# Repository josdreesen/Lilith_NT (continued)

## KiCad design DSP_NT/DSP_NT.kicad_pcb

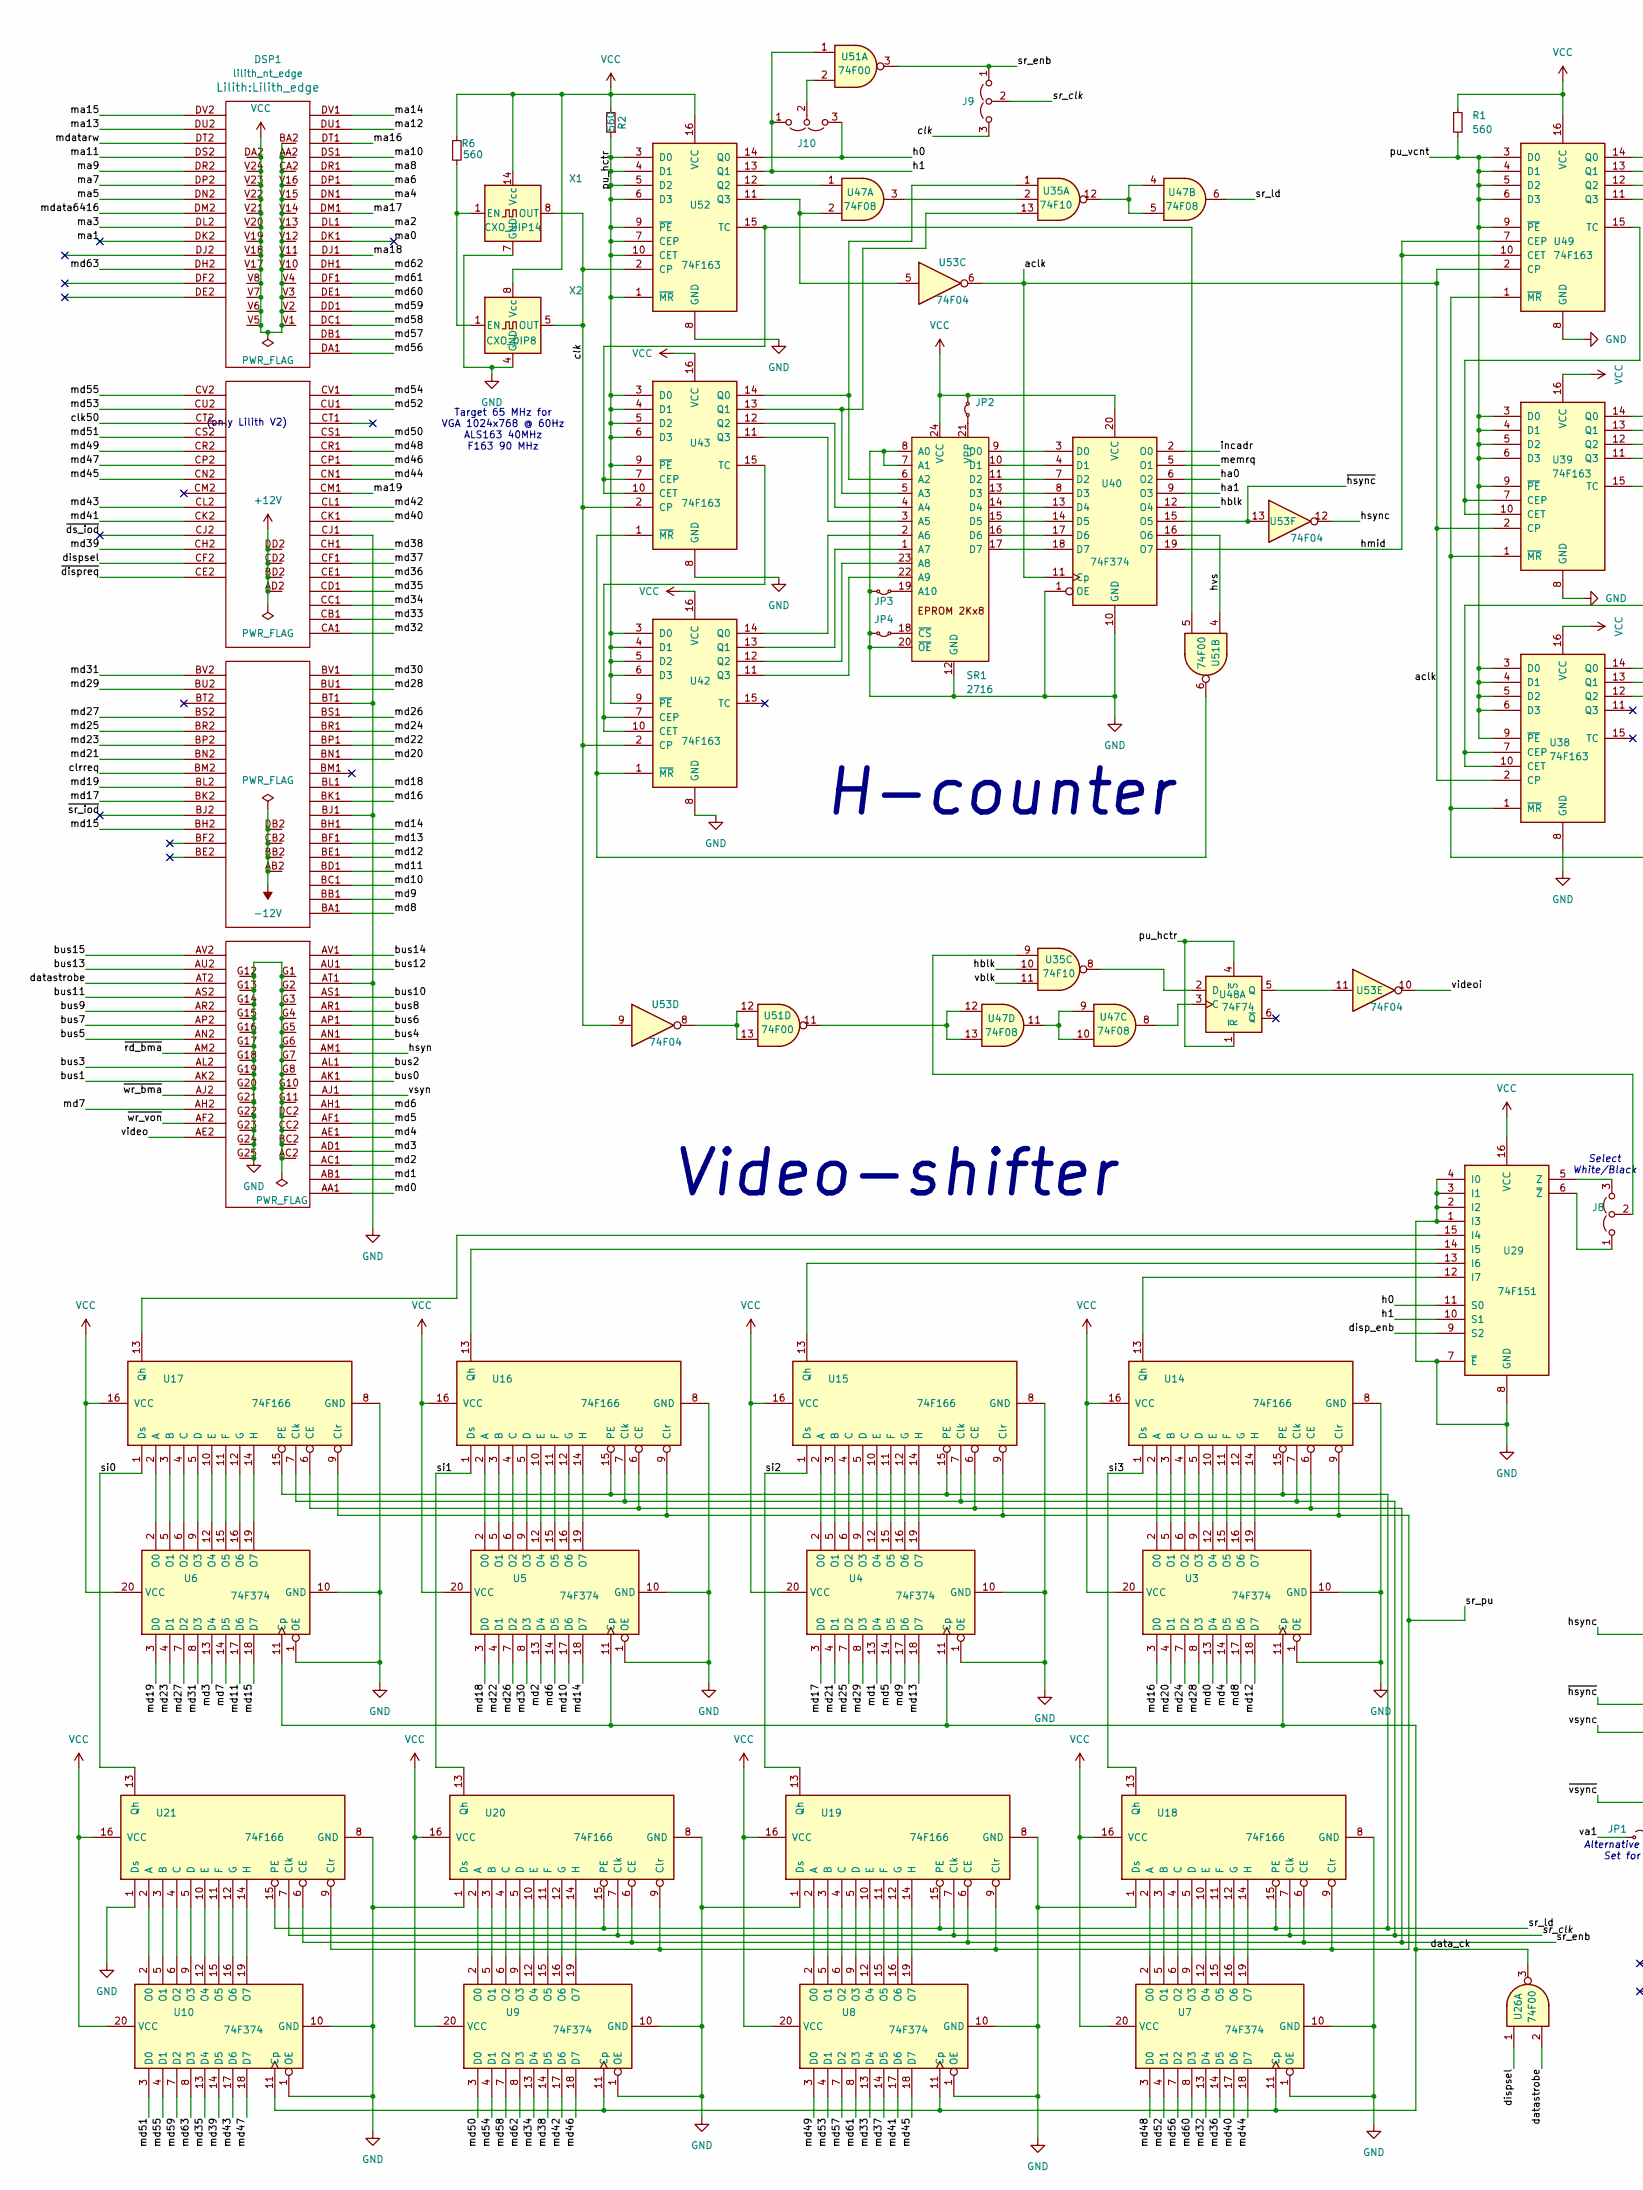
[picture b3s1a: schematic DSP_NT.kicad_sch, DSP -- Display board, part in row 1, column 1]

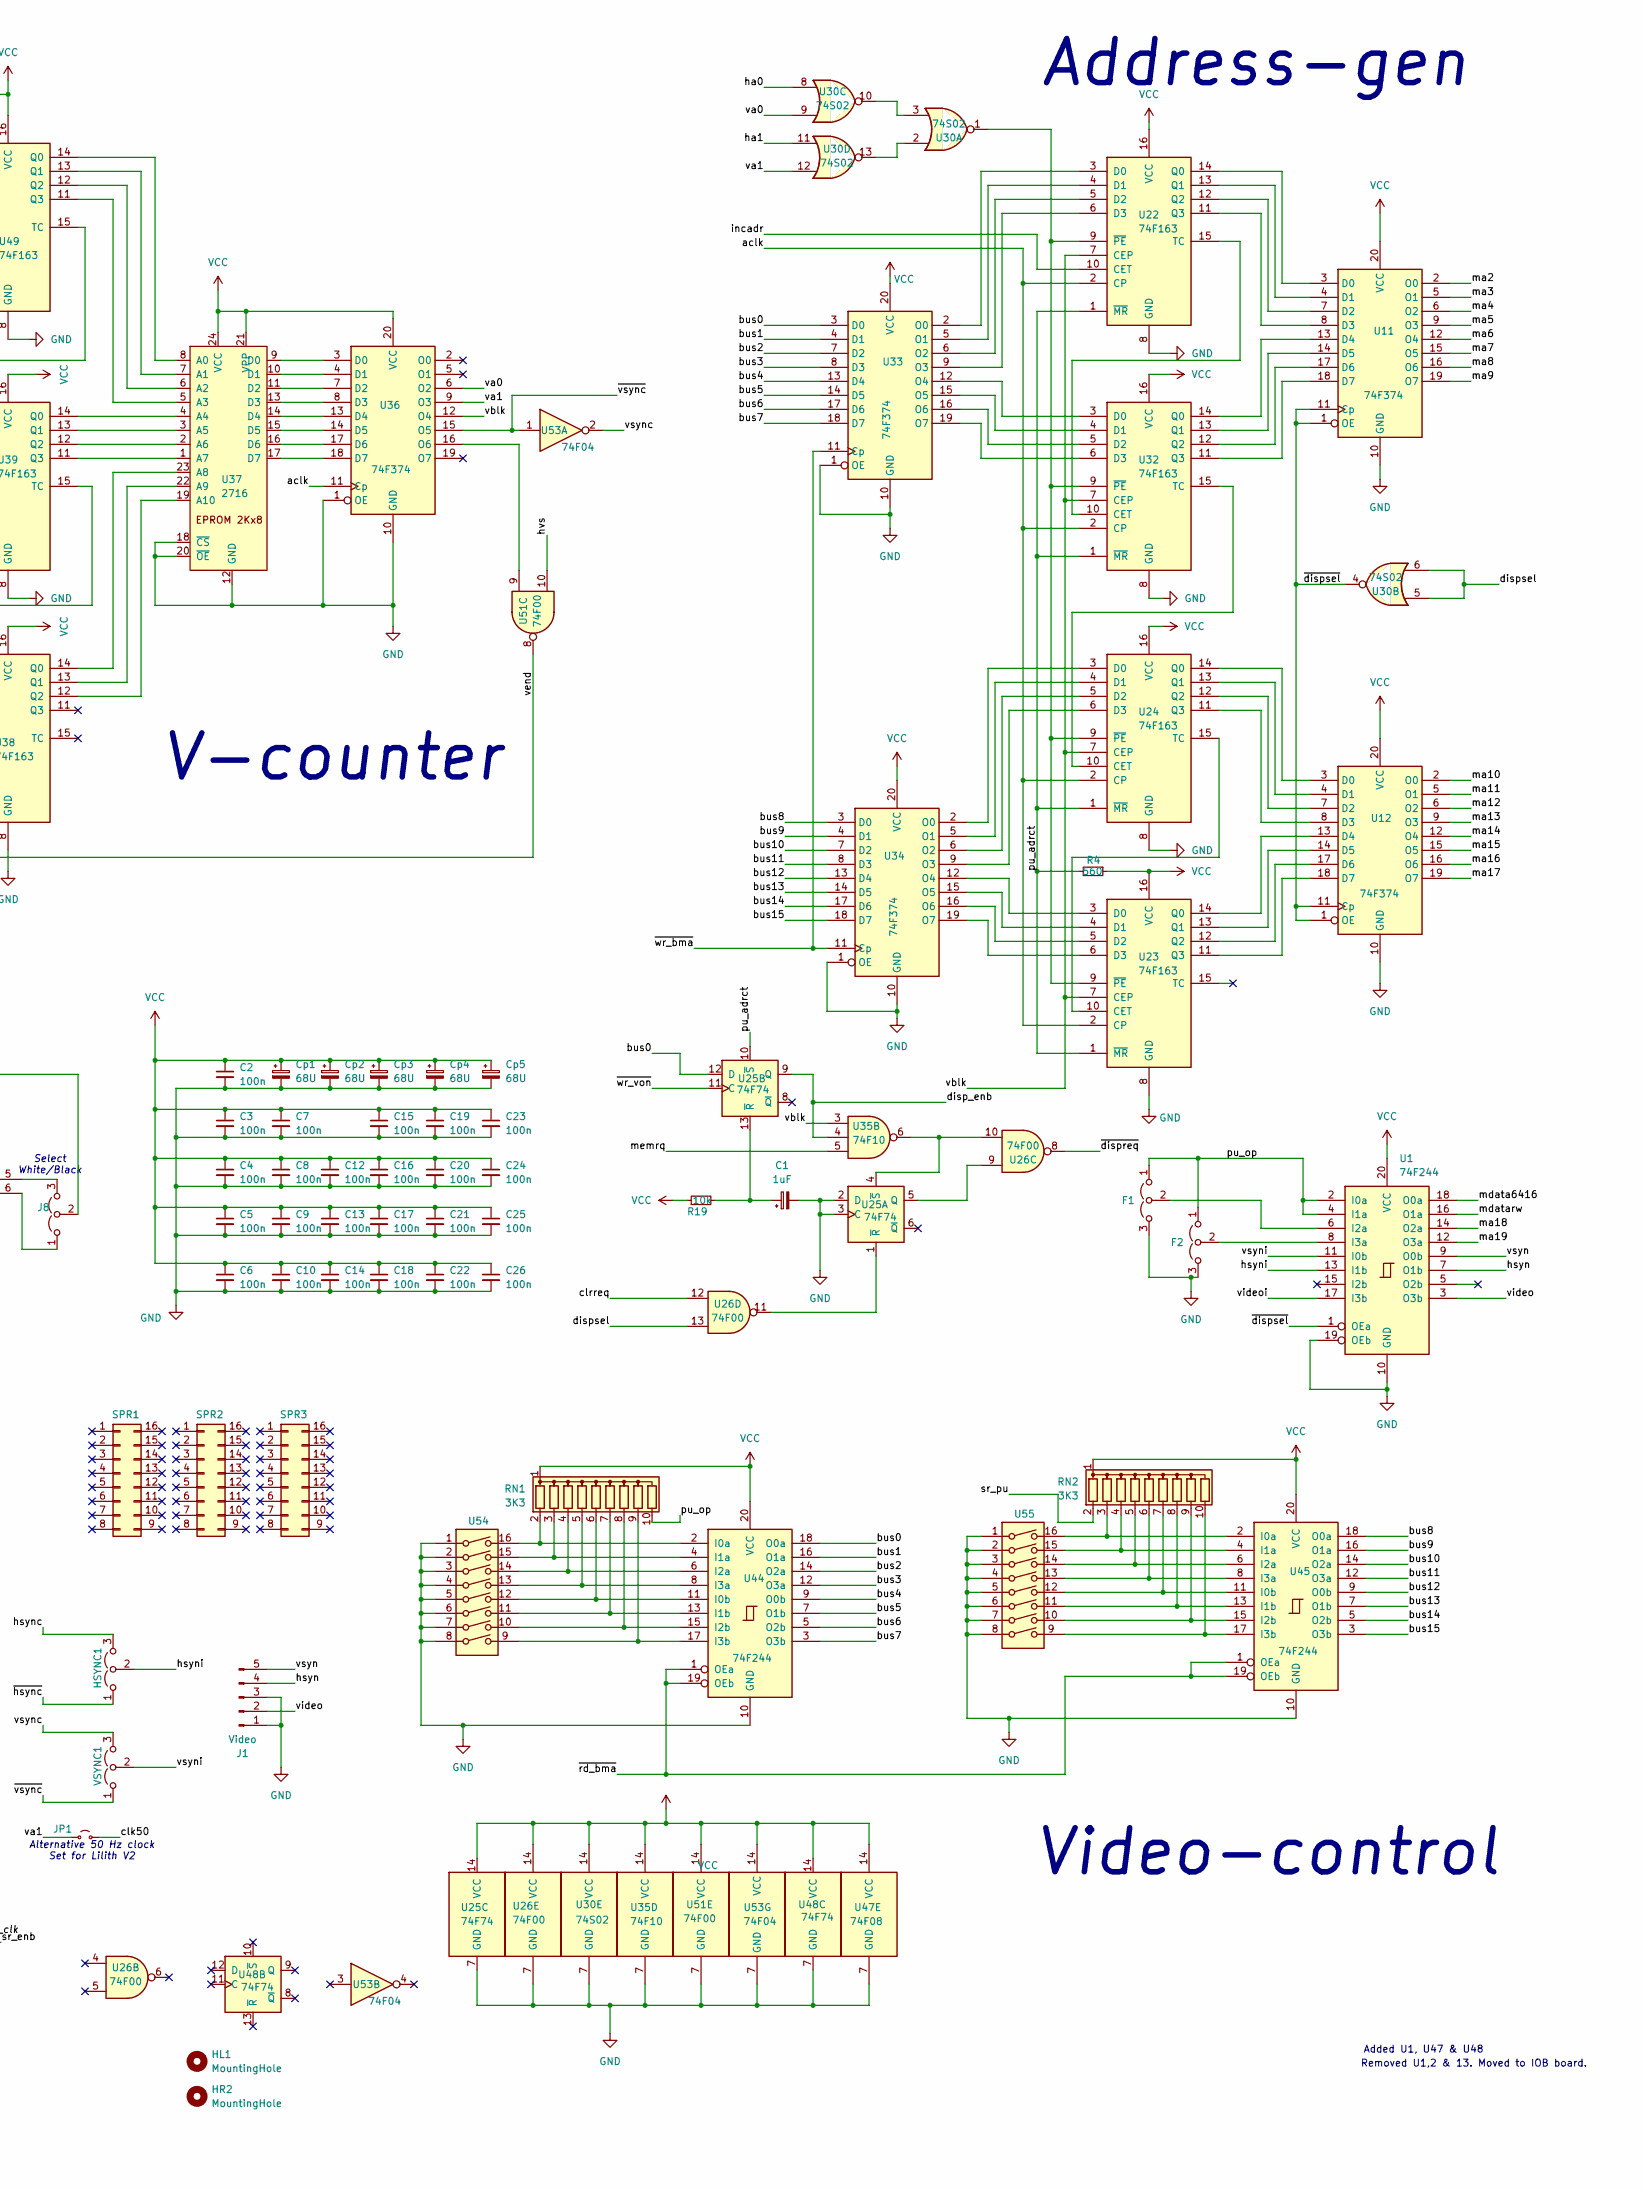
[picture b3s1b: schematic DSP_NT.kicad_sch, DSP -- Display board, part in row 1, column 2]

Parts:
C1: 1uF; CP_Radial_D4.0mm_P2.00mm
C2, C3, C4, C5, C6, C7, C8, C9, C10, C12, C13, C14, C15, C16, C17, C18, C19, C20, C21, C22, C23, C24, C25, C26: 100n; C_1206_3216Metric_Pad1.33x1.80mm_HandSolder
Cp1, Cp2, Cp3, Cp4, Cp5: 68U; CP_PHP
DSP1: lilith_nt_edge; Lilith_edge
F1, F2: Jumper_3_Open; PinHeader_1x03_P2.54mm_Vertical
HL1: MountingHole; Handle
HR2: MountingHole; Handle
HSYNC1: Jumper_3_Open; PinHeader_1x03_P2.54mm_Vertical
J1: Video; PinSocket_1x05_P2.54mm_Vertical
J8: Jumper_3_Open; SW_Push_1P2T_Vertical_E-Switch_800UDP8P1A1M6
J9, J10: Jumper_3_Open; PinHeader_1x03_P2.54mm_Vertical
JP1: Jumper_2_Small_Open; PinHeader_1x02_P2.54mm_Vertical
JP2, JP3, JP4: Jumper_2_Small_Bridged; SolderJumper-2_P1.3mm_Bridged_RoundedPad1.0x1.5mm
R1, R2, R4, R6: 560; R_Axial_DIN0207_L6.3mm_D2.5mm_P10.16mm_Horizontal
R19: 10k; R_Axial_DIN0207_L6.3mm_D2.5mm_P10.16mm_Horizontal
RN1, RN2: 3K3; R_Array_SIP10
SPR1, SPR2, SPR3: Conn_02x08_Counter_Clockwise; DIP-16_W7.62mm
SR1: 2716; DIP-24_W15.24mm_Socket
U1, U44, U45: 74F244; DIP-20_W7.62mm
U3, U4, U5, U6, U7, U8, U9, U10, U11, U12, U33, U34, U36, U40: 74F374; DIP-20_W7.62mm
U14, U15, U16, U17, U18, U19, U20, U21: 74F166; DIP-16_W7.62mm
U22, U23, U24, U32, U38, U39, U42, U43, U49, U52: 74F163; DIP-16_W7.62mm
U25, U48: 74F74; DIP-14_W7.62mm
U26, U51: 74F00; DIP-14_W7.62mm
U29: 74F151; DIP-16_W7.62mm
U30: 74S02; DIP-14_W7.62mm
U35: 74F10; DIP-14_W7.62mm
U37: 2716; DIP-24_W15.24mm_Socket
U47: 74F08; DIP-14_W7.62mm
U53: 74F04; DIP-14_W7.62mm
U54, U55: SW_DIP_x08; DIP-16_W7.62mm
VSYNC1: Jumper_3_Open; PinHeader_1x03_P2.54mm_Vertical
X1: CXO_DIP14; Oscillator_DIP-14
X2: CXO_DIP8; Oscillator_DIP-8

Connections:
+12V: DSP1.AD2, DSP1.BD2, DSP1.CD2, DSP1.DD2
-12V: DSP1.AB2, DSP1.BB2, DSP1.CB2, DSP1.DB2
/aclk: U22.2 (CP), U23.2 (CP), U24.2 (CP), U32.2 (CP), U36.11 (Cp), U38.2 (CP), U39.2 (CP), U40.11 (Cp), U49.2 (CP), U53.6
/bus0: DSP1.AK1, U25.12 (D), U33.3 (D0), U44.18 (O0a)
/bus1: DSP1.AK2, U33.4 (D1), U44.16 (O1a)
/bus2: DSP1.AL1, U33.7 (D2), U44.14 (O2a)
/bus3: DSP1.AL2, U33.8 (D3), U44.12 (O3a)
/bus4: DSP1.AN1, U33.13 (D4), U44.9 (O0b)
/bus5: DSP1.AN2, U33.14 (D5), U44.7 (O1b)
/bus6: DSP1.AP1, U33.17 (D6), U44.5 (O2b)
/bus7: DSP1.AP2, U33.18 (D7), U44.3 (O3b)
/bus8: DSP1.AR1, U34.3 (D0), U45.18 (O0a)
/bus9: DSP1.AR2, U34.4 (D1), U45.16 (O1a)
/bus10: DSP1.AS1, U34.7 (D2), U45.14 (O2a)
/bus11: DSP1.AS2, U34.8 (D3), U45.12 (O3a)
/bus12: DSP1.AU1, U34.13 (D4), U45.9 (O0b)
/bus13: DSP1.AU2, U34.14 (D5), U45.7 (O1b)
/bus14: DSP1.AV1, U34.17 (D6), U45.5 (O2b)
/bus15: DSP1.AV2, U34.18 (D7), U45.3 (O3b)
/clk: J9.3 (B), U42.2 (CP), U43.2 (CP), U52.2 (CP), U53.9, X1.8 (OUT), X2.5 (OUT)
/clk50: DSP1.CT2, JP1.2 (B)
/clrreq: DSP1.BM2, U26.12
/data_ck: U3.11 (Cp), U4.11 (Cp), U5.11 (Cp), U6.11 (Cp), U7.11 (Cp), U8.11 (Cp), U9.11 (Cp), U10.11 (Cp), U26.3
/datastrobe: DSP1.AT2, U26.2
/disp_enb: U25.9 (Q), U29.9 (S2), U35.4
/dispsel: DSP1.CF2, U26.1, U26.13, U30.5, U30.6
/h0: J10.3 (B), U29.11 (S0), U52.14 (Q0)
/h1: J10.1 (A), U29.10 (S1), U51.1, U52.13 (Q1)
/ha0: U30.8, U40.6 (O2)
/ha1: U30.11, U40.9 (O3)
/hblk: U35.10, U40.12 (O4)
/hmid: U40.19 (O7), U49.7 (CEP), U49.10 (CET)
/hsyn: DSP1.AM1, J1.4, U1.7 (O1b)
/hsync: HSYNC1.3 (B), U53.12
/hsyni: HSYNC1.2 (C), U1.13 (I1b)
/hvs: U40.16 (O6), U51.4, U51.10
/incadr: U22.10 (CET), U40.2 (O0)
/ma0: DSP1.DK1
/ma1: DSP1.DK2
/ma2: DSP1.DL1, U11.2 (O0)
/ma3: DSP1.DL2, U11.5 (O1)
/ma4: DSP1.DN1, U11.6 (O2)
/ma5: DSP1.DN2, U11.9 (O3)
/ma6: DSP1.DP1, U11.12 (O4)
/ma7: DSP1.DP2, U11.15 (O5)
/ma8: DSP1.DR1, U11.16 (O6)
/ma9: DSP1.DR2, U11.19 (O7)
/ma10: DSP1.DS1, U12.2 (O0)
/ma11: DSP1.DS2, U12.5 (O1)
/ma12: DSP1.DU1, U12.6 (O2)
/ma13: DSP1.DU2, U12.9 (O3)
/ma14: DSP1.DV1, U12.12 (O4)
/ma15: DSP1.DV2, U12.15 (O5)
/ma16: DSP1.DT1, U12.16 (O6)
/ma17: DSP1.DM1, U12.19 (O7)
/ma18: DSP1.DJ1, U1.14 (O2a)
/ma19: DSP1.CM1, U1.12 (O3a)
/md0: DSP1.AA1, U3.13 (D4)
/md1: DSP1.AB1, U4.13 (D4)
/md2: DSP1.AC1, U5.13 (D4)
/md3: DSP1.AD1, U6.13 (D4)
/md4: DSP1.AE1, U3.14 (D5)
/md5: DSP1.AF1, U4.14 (D5)
/md6: DSP1.AH1, U5.14 (D5)
/md7: DSP1.AH2, U6.14 (D5)
/md8: DSP1.BA1, U3.17 (D6)
/md9: DSP1.BB1, U4.17 (D6)
/md10: DSP1.BC1, U5.17 (D6)
/md11: DSP1.BD1, U6.17 (D6)
/md12: DSP1.BE1, U3.18 (D7)
/md13: DSP1.BF1, U4.18 (D7)
/md14: DSP1.BH1, U5.18 (D7)
/md15: DSP1.BH2, U6.18 (D7)
/md16: DSP1.BK1, U3.3 (D0)
/md17: DSP1.BK2, U4.3 (D0)
/md18: DSP1.BL1, U5.3 (D0)
/md19: DSP1.BL2, U6.3 (D0)
/md20: DSP1.BN1, U3.4 (D1)
/md21: DSP1.BN2, U4.4 (D1)
/md22: DSP1.BP1, U5.4 (D1)
/md23: DSP1.BP2, U6.4 (D1)
/md24: DSP1.BR1, U3.7 (D2)
/md25: DSP1.BR2, U4.7 (D2)
/md26: DSP1.BS1, U5.7 (D2)
/md27: DSP1.BS2, U6.7 (D2)
/md28: DSP1.BU1, U3.8 (D3)
/md29: DSP1.BU2, U4.8 (D3)
/md30: DSP1.BV1, U5.8 (D3)
/md31: DSP1.BV2, U6.8 (D3)
/md32: DSP1.CA1, U7.13 (D4)
/md33: DSP1.CB1, U8.13 (D4)
/md34: DSP1.CC1, U9.13 (D4)
/md35: DSP1.CD1, U10.13 (D4)
/md36: DSP1.CE1, U7.14 (D5)
/md37: DSP1.CF1, U8.14 (D5)
/md38: DSP1.CH1, U9.14 (D5)
/md39: DSP1.CH2, U10.14 (D5)
/md40: DSP1.CK1, U7.17 (D6)
/md41: DSP1.CK2, U8.17 (D6)
/md42: DSP1.CL1, U9.17 (D6)
/md43: DSP1.CL2, U10.17 (D6)
/md44: DSP1.CN1, U7.18 (D7)
/md45: DSP1.CN2, U8.18 (D7)
/md46: DSP1.CP1, U9.18 (D7)
/md47: DSP1.CP2, U10.18 (D7)
/md48: DSP1.CR1, U7.3 (D0)
/md49: DSP1.CR2, U8.3 (D0)
/md50: DSP1.CS1, U9.3 (D0)
/md51: DSP1.CS2, U10.3 (D0)
/md52: DSP1.CU1, U7.4 (D1)
/md53: DSP1.CU2, U8.4 (D1)
/md54: DSP1.CV1, U9.4 (D1)
/md55: DSP1.CV2, U10.4 (D1)
/md56: DSP1.DA1, U7.7 (D2)
/md57: DSP1.DB1, U8.7 (D2)
/md58: DSP1.DC1, U9.7 (D2)
/md59: DSP1.DD1, U10.7 (D2)
/md60: DSP1.DE1, U7.8 (D3)
/md61: DSP1.DF1, U8.8 (D3)
/md62: DSP1.DH1, U9.8 (D3)
/md63: DSP1.DH2, U10.8 (D3)
/mdata6416: DSP1.DM2, U1.18 (O0a)
/mdatarw: DSP1.DT2, U1.16 (O1a)
/memrq: U35.5, U40.5 (O1)
/pu_adrct: R4.2, U22.1 (~MR), U23.1 (~MR), U24.1 (~MR), U25.10 (~S), U32.1 (~MR)
/pu_hctr: R2.1, U42.3 (D0), U42.4 (D1), U42.5 (D2), U42.6 (D3), U42.9 (~PE), U43.3 (D0), U43.4 (D1), U43.5 (D2), U43.6 (D3), U43.9 (~PE), U48.1 (~R), U48.4 (~S), U52.1 (~MR), U52.3 (D0), U52.4 (D1), U52.5 (D2), U52.6 (D3), U52.7 (CEP), U52.9 (~PE), U52.10 (CET)
/pu_op: F1.1 (A), F2.1 (A), RN1.10 (R9), U1.2 (I0a), U1.4 (I1a); also elsewhere on the board
/pu_vcnt: R1.2, U38.3 (D0), U38.4 (D1), U38.5 (D2), U38.6 (D3), U38.9 (~PE), U39.3 (D0), U39.4 (D1), U39.5 (D2), U39.6 (D3), U39.9 (~PE), U49.3 (D0), U49.4 (D1), U49.5 (D2), U49.6 (D3), U49.9 (~PE)
/si0: U17.1 (Ds), U21.13 (Qh)
/si1: U16.1 (Ds), U20.13 (Qh)
/si2: U15.1 (Ds), U19.13 (Qh)
/si3: U14.1 (Ds), U18.13 (Qh)
/sr_clk: J9.2 (C), U14.7 (Clk), U15.7 (Clk), U16.7 (Clk), U17.7 (Clk), U18.7 (Clk), U19.7 (Clk), U20.7 (Clk), U21.7 (Clk)
/sr_enb: J9.1 (A), U14.6 (CE), U15.6 (CE), U16.6 (CE), U17.6 (CE), U18.6 (CE), U19.6 (CE), U20.6 (CE), U21.6 (CE), U51.3
/sr_ld: U14.15 (PE), U15.15 (PE), U16.15 (PE), U17.15 (PE), U18.15 (PE), U19.15 (PE), U20.15 (PE), U21.15 (PE), U47.6
/sr_pu: RN2.2 (R1), U14.9 (Clr), U15.9 (Clr), U16.9 (Clr), U17.9 (Clr), U18.9 (Clr), U19.9 (Clr), U20.9 (Clr), U21.9 (Clr)
/va0: U30.9, U36.6 (O2)
/va1: JP1.1 (A), U30.12, U36.9 (O3)
/vblk: U22.7 (CEP), U23.7 (CEP), U24.7 (CEP), U32.7 (CEP), U35.3, U35.11, U36.12 (O4)
/vend: U38.1 (~MR), U39.1 (~MR), U49.1 (~MR), U51.8
/video: DSP1.AE2, J1.2, U1.3 (O3b)
/videoi: U1.17 (I3b), U53.10
/vsyn: DSP1.AJ1, J1.5, U1.9 (O0b)
/vsync: U53.2, VSYNC1.3 (B)
/vsyni: U1.11 (I0b), VSYNC1.2 (C)
/~dispreq: DSP1.CE2, U26.8
/~dispsel: U1.1 (OEa), U11.1 (OE), U11.11 (Cp), U12.1 (OE), U12.11 (Cp), U30.4
/~ds_iod: DSP1.CJ2
/~hsync: HSYNC1.1 (A), U40.15 (O5), U53.13
/~rd_bma: DSP1.AM2, U44.1 (OEa), U44.19 (OEb), U45.1 (OEa), U45.19 (OEb)
/~sr_iod: DSP1.BJ2
/~vsync: U36.15 (O5), U53.1, VSYNC1.1 (A)
/~wr_bma: DSP1.AJ2, U33.11 (Cp), U34.11 (Cp)
/~wr_von: DSP1.AF2, U25.11 (C)
GND: C1.2, C2.2, C3.2, C4.2, C5.2, C6.2, C7.2, C8.2, C9.2, C10.2, C12.2, C13.2, C14.2, C15.2, C16.2, C17.2, C18.2, C19.2, C20.2, C21.2, C22.2, C23.2, C24.2, C25.2, C26.2, Cp1.2, Cp2.2, Cp3.2, Cp4.2, Cp5.2, DSP1.AC2, DSP1.AT1, DSP1.BC2, DSP1.BJ1, DSP1.BT1, DSP1.CC2, DSP1.CJ1, DSP1.DC2, DSP1.G1 (GND), DSP1.G2 (GND), DSP1.G3 (GND), DSP1.G4 (GND), DSP1.G5 (GND), DSP1.G6 (GND), DSP1.G7 (GND), DSP1.G8 (GND), DSP1.G10, DSP1.G11, DSP1.G12, DSP1.G13, DSP1.G14, DSP1.G15, DSP1.G16, DSP1.G17, DSP1.G18, DSP1.G19, DSP1.G20, DSP1.G21, DSP1.G22, DSP1.G23, DSP1.G24, DSP1.G25, F1.3 (B), F2.3 (B), J1.1, J1.3, JP3.2 (B), JP4.2 (B), SR1.7 (A1), SR1.8 (A0), SR1.12 (GND), SR1.20 (~OE), U1.10 (GND), U1.19 (OEb), U3.1 (OE), U3.10 (GND), U4.1 (OE), U4.10 (GND), U5.1 (OE), U5.10 (GND), U6.1 (OE), U6.10 (GND), U7.1 (OE), U7.10 (GND), U8.1 (OE), U8.10 (GND), U9.1 (OE), U9.10 (GND), U10.1 (OE), U10.10 (GND), U11.10 (GND), U12.10 (GND), U14.8 (GND), U15.8 (GND), U16.8 (GND), U17.8 (GND), U18.1 (Ds), U18.8 (GND), U19.1 (Ds), U19.8 (GND), U20.1 (Ds), U20.8 (GND), U21.1 (Ds), U21.8 (GND), U22.8 (GND), U23.8 (GND), U24.8 (GND), U25.2 (D), U25.3 (C), U25.7 (GND), U26.7 (GND), U29.1 (I3), U29.2 (I2), U29.3 (I1), U29.4 (I0), U29.7 (~E), U29.8 (GND), U30.7 (GND), U32.8 (GND), U33.1 (OE), U33.10 (GND), U34.1 (OE), U34.10 (GND), U35.7 (GND), U36.1 (OE), U36.10 (GND), U37.12 (GND), U37.18 (~CS), U37.20 (~OE), U38.8 (GND), U39.8 (GND), U40.1 (OE), U40.10 (GND), U42.8 (GND), U43.8 (GND), U44.10 (GND), U45.10 (GND), U47.7 (GND), U48.7 (GND), U49.8 (GND), U51.7 (GND), U52.8 (GND), U53.7 (GND), U54.1, U54.2, U54.3, U54.4, U54.5, U54.6, U54.7, U54.8, U55.1, U55.2, U55.3, U55.4, U55.5, U55.6, U55.7, U55.8, X1.7 (GND), X2.4 (GND); also elsewhere on the board
unnamed 155: F1.2 (C), U1.6 (I2a); also elsewhere on the board
unnamed 156: F2.2 (C), U1.8 (I3a); also elsewhere on the board
unnamed: J8.1 (A), U29.6 (~Z)
unnamed: J8.3 (B), U29.5 (Z)
unnamed: J8.2 (C), U35.9
unnamed: J10.2 (C), U51.2
unnamed: JP2.1 (A), SR1.21 (VPP)
unnamed: JP3.1 (A), SR1.19 (A10)
unnamed: JP4.1 (A), SR1.18 (~CS)
unnamed: RN1.2 (R1), U44.2 (I0a), U54.16
unnamed: RN1.3 (R2), U44.4 (I1a), U54.15
unnamed: RN1.4 (R3), U44.6 (I2a), U54.14
unnamed: RN1.5 (R4), U44.8 (I3a), U54.13
unnamed: RN1.6 (R5), U44.11 (I0b), U54.12
unnamed: RN1.7 (R6), U44.13 (I1b), U54.11
unnamed: RN1.8 (R7), U44.15 (I2b), U54.10
unnamed: RN1.9 (R8), U44.17 (I3b), U54.9
unnamed: RN2.3 (R2), U45.2 (I0a), U55.16
unnamed: RN2.4 (R3), U45.4 (I1a), U55.15
unnamed: RN2.5 (R4), U45.6 (I2a), U55.14
unnamed: RN2.6 (R5), U45.8 (I3a), U55.13
unnamed: RN2.7 (R6), U45.11 (I0b), U55.12
unnamed: RN2.8 (R7), U45.13 (I1b), U55.11
unnamed: RN2.9 (R8), U45.15 (I2b), U55.10
unnamed: RN2.10 (R9), U45.17 (I3b), U55.9
unnamed: SR1.6 (A2), U35.1, U43.14 (Q0)
unnamed: SR1.5 (A3), U35.13, U43.13 (Q1)
unnamed: SR1.4 (A4), U43.12 (Q2)
unnamed: SR1.3 (A5), U43.11 (Q3)
unnamed: SR1.2 (A6), U42.14 (Q0)
unnamed: SR1.1 (A7), U42.13 (Q1)
unnamed: SR1.23 (A8), U42.12 (Q2)
unnamed: SR1.22 (A9), U42.11 (Q3)
unnamed: SR1.9 (D0), U40.3 (D0)
unnamed: SR1.10 (D1), U40.4 (D1)
unnamed: SR1.11 (D2), U40.7 (D2)
unnamed: SR1.13 (D3), U40.8 (D3)
unnamed: SR1.14 (D4), U40.13 (D4)
unnamed: SR1.15 (D5), U40.14 (D5)
unnamed: SR1.16 (D6), U40.17 (D6)
unnamed: SR1.17 (D7), U40.18 (D7)
unnamed: U10.2 (O0), U21.2 (A)
unnamed: U10.5 (O1), U21.3 (B)
unnamed: U10.6 (O2), U21.4 (C)
unnamed: U10.9 (O3), U21.5 (D)
unnamed: U10.12 (O4), U21.10 (E)
unnamed: U10.15 (O5), U21.11 (F)
unnamed: U10.16 (O6), U21.12 (G)
unnamed: U10.19 (O7), U21.14 (H)
unnamed: U11.3 (D0), U22.14 (Q0)
unnamed: U11.4 (D1), U22.13 (Q1)
unnamed: U11.7 (D2), U22.12 (Q2)
unnamed: U11.8 (D3), U22.11 (Q3)
unnamed: U11.13 (D4), U32.14 (Q0)
unnamed: U11.14 (D5), U32.13 (Q1)
unnamed: U11.17 (D6), U32.12 (Q2)
unnamed: U11.18 (D7), U32.11 (Q3)
unnamed: U12.3 (D0), U24.14 (Q0)
unnamed: U12.4 (D1), U24.13 (Q1)
unnamed: U12.7 (D2), U24.12 (Q2)
unnamed: U12.8 (D3), U24.11 (Q3)
unnamed: U12.13 (D4), U23.14 (Q0)
unnamed: U12.14 (D5), U23.13 (Q1)
unnamed: U12.17 (D6), U23.12 (Q2)
unnamed: U12.18 (D7), U23.11 (Q3)
unnamed: U3.2 (O0), U14.2 (A)
unnamed: U3.5 (O1), U14.3 (B)
unnamed: U3.6 (O2), U14.4 (C)
unnamed: U3.9 (O3), U14.5 (D)
unnamed: U3.12 (O4), U14.10 (E)
unnamed: U3.15 (O5), U14.11 (F)
unnamed: U3.16 (O6), U14.12 (G)
unnamed: U3.19 (O7), U14.14 (H)
unnamed: U14.13 (Qh), U29.12 (I7)
unnamed: U4.2 (O0), U15.2 (A)
unnamed: U4.5 (O1), U15.3 (B)
unnamed: U4.6 (O2), U15.4 (C)
unnamed: U4.9 (O3), U15.5 (D)
unnamed: U4.12 (O4), U15.10 (E)
unnamed: U4.15 (O5), U15.11 (F)
unnamed: U4.16 (O6), U15.12 (G)
unnamed: U4.19 (O7), U15.14 (H)
unnamed: U15.13 (Qh), U29.13 (I6)
unnamed: U5.2 (O0), U16.2 (A)
unnamed: U5.5 (O1), U16.3 (B)
unnamed: U5.6 (O2), U16.4 (C)
unnamed: U5.9 (O3), U16.5 (D)
unnamed: U5.12 (O4), U16.10 (E)
unnamed: U5.15 (O5), U16.11 (F)
unnamed: U5.16 (O6), U16.12 (G)
unnamed: U5.19 (O7), U16.14 (H)
unnamed: U16.13 (Qh), U29.14 (I5)
unnamed: U6.2 (O0), U17.2 (A)
unnamed: U6.5 (O1), U17.3 (B)
unnamed: U6.6 (O2), U17.4 (C)
unnamed: U6.9 (O3), U17.5 (D)
unnamed: U6.12 (O4), U17.10 (E)
unnamed: U6.15 (O5), U17.11 (F)
unnamed: U6.16 (O6), U17.12 (G)
unnamed: U6.19 (O7), U17.14 (H)
unnamed: U17.13 (Qh), U29.15 (I4)
unnamed: U7.2 (O0), U18.2 (A)
unnamed: U7.5 (O1), U18.3 (B)
unnamed: U7.6 (O2), U18.4 (C)
unnamed: U7.9 (O3), U18.5 (D)
unnamed: U7.12 (O4), U18.10 (E)
unnamed: U7.15 (O5), U18.11 (F)
unnamed: U7.16 (O6), U18.12 (G)
unnamed: U7.19 (O7), U18.14 (H)
unnamed: U8.2 (O0), U19.2 (A)
unnamed: U8.5 (O1), U19.3 (B)
unnamed: U8.6 (O2), U19.4 (C)
unnamed: U8.9 (O3), U19.5 (D)
unnamed: U8.12 (O4), U19.10 (E)
unnamed: U8.15 (O5), U19.11 (F)
unnamed: U8.16 (O6), U19.12 (G)
unnamed: U8.19 (O7), U19.14 (H)
unnamed: U9.2 (O0), U20.2 (A)
unnamed: U9.5 (O1), U20.3 (B)
unnamed: U9.6 (O2), U20.4 (C)
unnamed: U9.9 (O3), U20.5 (D)
unnamed: U9.12 (O4), U20.10 (E)
unnamed: U9.15 (O5), U20.11 (F)
unnamed: U9.16 (O6), U20.12 (G)
unnamed: U9.19 (O7), U20.14 (H)
unnamed: U22.3 (D0), U33.2 (O0)
unnamed: U22.4 (D1), U33.5 (O1)
unnamed: U22.5 (D2), U33.6 (O2)
unnamed: U22.6 (D3), U33.9 (O3)
unnamed: U22.15 (TC), U32.10 (CET)
unnamed: U22.9 (~PE), U23.9 (~PE), U24.9 (~PE), U30.1, U32.9 (~PE)
unnamed: U23.10 (CET), U24.15 (TC)
unnamed: U23.3 (D0), U34.12 (O4)
unnamed: U23.4 (D1), U34.15 (O5)
unnamed: U23.5 (D2), U34.16 (O6)
unnamed: U23.6 (D3), U34.19 (O7)
unnamed: U24.10 (CET), U32.15 (TC)
unnamed: U24.3 (D0), U34.2 (O0)
unnamed: U24.4 (D1), U34.5 (O1)
unnamed: U24.5 (D2), U34.6 (O2)
unnamed: U24.6 (D3), U34.9 (O3)
unnamed: U25.5 (Q), U26.9
unnamed: U25.1 (~R), U26.11
unnamed: U25.4 (~S), U26.10, U35.6
unnamed: C1.1, R19.2, U25.13 (~R)
unnamed: U30.3, U30.10
unnamed: U30.2, U30.13
unnamed: U32.3 (D0), U33.12 (O4)
unnamed: U32.4 (D1), U33.15 (O5)
unnamed: U32.5 (D2), U33.16 (O6)
unnamed: U32.6 (D3), U33.19 (O7)
unnamed: U35.2, U47.3
unnamed: U35.12, U47.4, U47.5
unnamed: U36.3 (D0), U37.9 (D0)
unnamed: U36.4 (D1), U37.10 (D1)
unnamed: U36.7 (D2), U37.11 (D2)
unnamed: U36.8 (D3), U37.13 (D3)
unnamed: U36.13 (D4), U37.14 (D4)
unnamed: U36.14 (D5), U37.15 (D5)
unnamed: U36.17 (D6), U37.16 (D6)
unnamed: U36.18 (D7), U37.17 (D7)
unnamed: U36.16 (O6), U51.9
unnamed: U37.8 (A0), U49.14 (Q0)
unnamed: U37.7 (A1), U49.13 (Q1)
unnamed: U37.6 (A2), U49.12 (Q2)
unnamed: U37.5 (A3), U49.11 (Q3)
unnamed: U37.4 (A4), U39.14 (Q0)
unnamed: U37.3 (A5), U39.13 (Q1)
unnamed: U37.2 (A6), U39.12 (Q2)
unnamed: U37.1 (A7), U39.11 (Q3)
unnamed: U37.23 (A8), U38.14 (Q0)
unnamed: U37.22 (A9), U38.13 (Q1)
unnamed: U37.19 (A10), U38.12 (Q2)
unnamed: U38.7 (CEP), U38.10 (CET), U39.15 (TC)
unnamed: U39.7 (CEP), U39.10 (CET), U49.15 (TC)
unnamed: U42.7 (CEP), U42.10 (CET), U43.15 (TC)
unnamed: U42.1 (~MR), U43.1 (~MR), U51.6
unnamed: U43.7 (CEP), U43.10 (CET), U51.5, U52.15 (TC)
unnamed: U47.9, U47.10, U47.11
unnamed: U47.12, U47.13, U51.11
unnamed: U47.8, U48.3 (C)
unnamed: U35.8, U48.2 (D)
unnamed: U48.5 (Q), U53.11
unnamed: U51.12, U51.13, U53.8
unnamed: U47.1, U52.12 (Q2)
unnamed: U47.2, U52.11 (Q3), U53.5
unnamed: R6.2, X1.1 (EN), X2.1 (EN)
VCC: C2.1, C3.1, C4.1, C5.1, C6.1, C7.1, C8.1, C9.1, C10.1, C12.1, C13.1, C14.1, C15.1, C16.1, C17.1, C18.1, C19.1, C20.1, C21.1, C22.1, C23.1, C24.1, C25.1, C26.1, Cp1.1, Cp2.1, Cp3.1, Cp4.1, Cp5.1, DSP1.AA2, DSP1.BA2, DSP1.CA2, DSP1.DA2, DSP1.V1 (VCC), DSP1.V2 (VCC), DSP1.V3 (VCC), DSP1.V4 (VCC), DSP1.V5 (VCC), DSP1.V6 (VCC), DSP1.V7 (VCC), DSP1.V8 (VCC), DSP1.V10, DSP1.V11, DSP1.V12, DSP1.V13, DSP1.V14, DSP1.V15, DSP1.V16, DSP1.V17, DSP1.V18, DSP1.V19, DSP1.V20, DSP1.V21, DSP1.V22, DSP1.V23, DSP1.V24, JP2.2 (B), R1.1, R2.2, R4.1, R6.1, R19.1, RN1.1 (common), RN2.1 (common), SR1.24 (VCC), U1.20 (VCC), U3.20 (VCC), U4.20 (VCC), U5.20 (VCC), U6.20 (VCC), U7.20 (VCC), U8.20 (VCC), U9.20 (VCC), U10.20 (VCC), U11.20 (VCC), U12.20 (VCC), U14.16 (VCC), U15.16 (VCC), U16.16 (VCC), U17.16 (VCC), U18.16 (VCC), U19.16 (VCC), U20.16 (VCC), U21.16 (VCC), U22.16 (VCC), U23.16 (VCC), U24.16 (VCC), U25.14 (VCC), U26.14 (VCC), U29.16 (VCC), U30.14 (VCC), U32.16 (VCC), U33.20 (VCC), U34.20 (VCC), U35.14 (VCC), U36.20 (VCC), U37.21 (VPP), U37.24 (VCC), U38.16 (VCC), U39.16 (VCC), U40.20 (VCC), U42.16 (VCC), U43.16 (VCC), U44.20 (VCC), U45.20 (VCC), U47.14 (VCC), U48.14 (VCC), U49.16 (VCC), U51.14 (VCC), U52.16 (VCC), U53.14 (VCC), X1.14 (Vcc), X2.8 (Vcc)

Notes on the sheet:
Address-gen
Target 65 MHz for VGA 1024x768 @ 60Hz ALS163 40MHz F163 90 MHz
Added U1, U47 & U48
Alternative 50 Hz clock Set for Lilith V2
Removed U1,2 & 13. Moved to IOB board.
Video-shifter
(only Lilith V2)
H-counter
Video-control
Select White/Black
V-counter

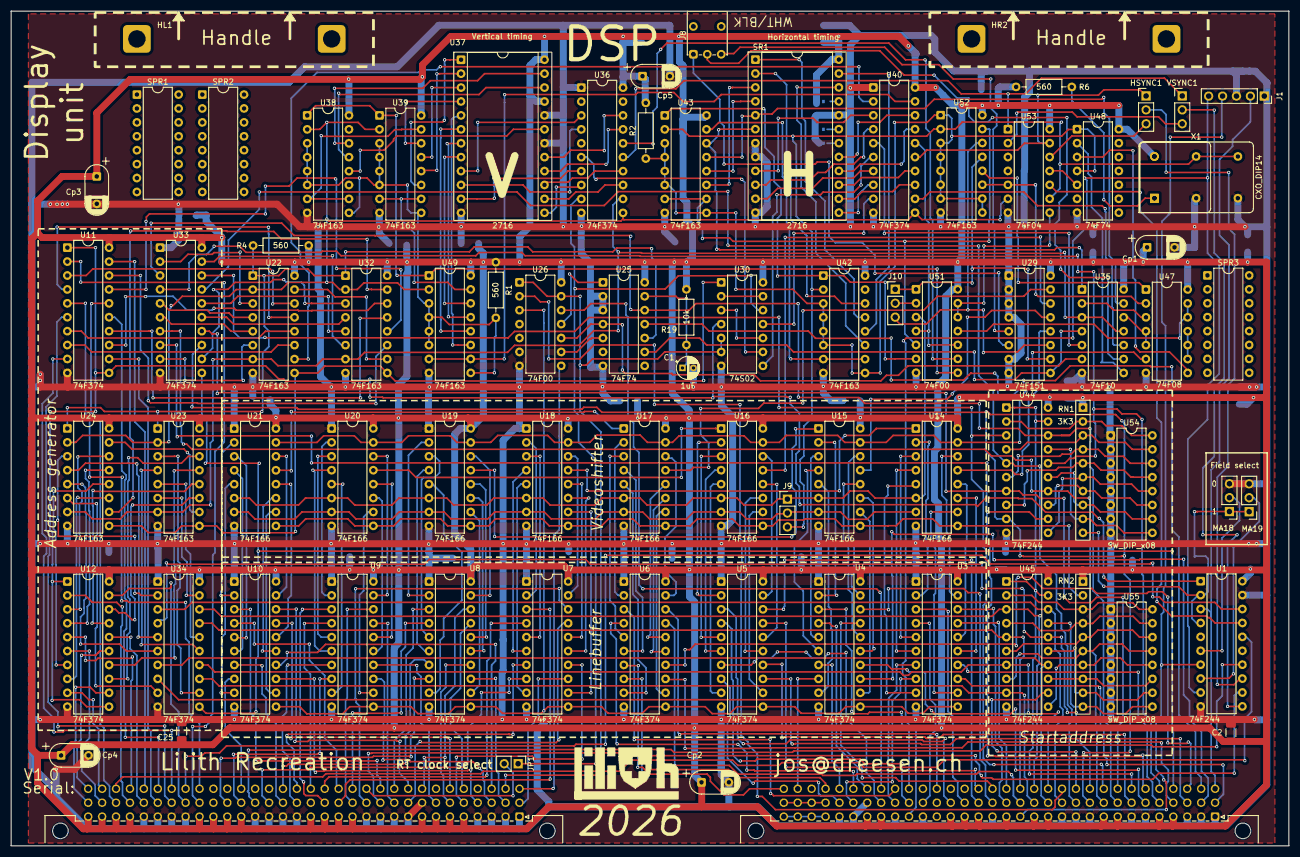
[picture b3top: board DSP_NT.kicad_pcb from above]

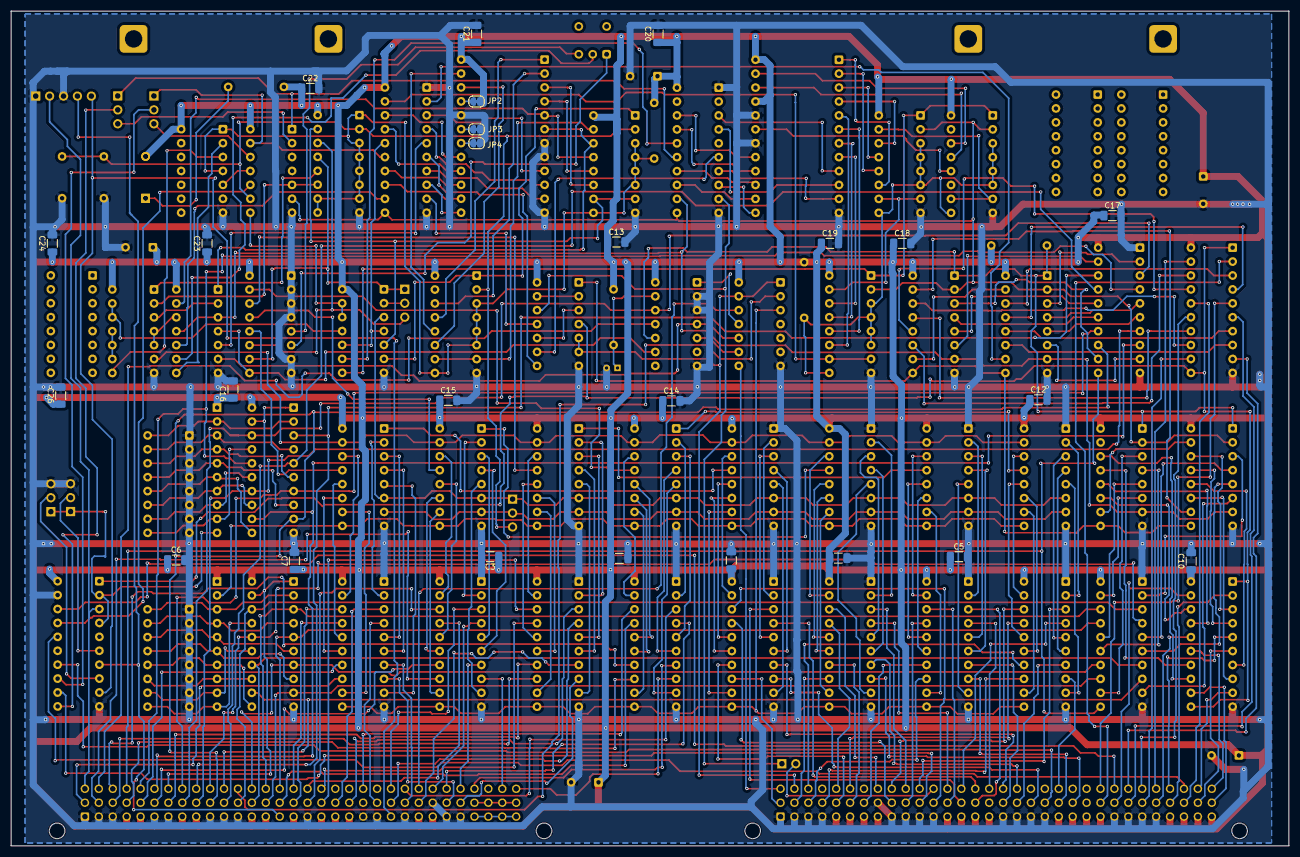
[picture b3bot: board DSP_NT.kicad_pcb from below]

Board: 2 copper layers, 233.3 x 152.4 mm, 105 parts (25 on the bottom side), 339 nets.

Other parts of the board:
MA18, MA19: Jumper_3_Open; PinHeader_1x03_P2.54mm_Vertical

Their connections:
/pu_op: MA18.1 (A), MA19.1 (A); also elsewhere on the board
GND: MA18.3 (B), MA19.3 (B); also elsewhere on the board
unnamed 155: MA18.2 (C); also elsewhere on the board
unnamed 156: MA19.2 (C); also elsewhere on the board
